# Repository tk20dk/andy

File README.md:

# andy
Audio interface for Krieger prototype board

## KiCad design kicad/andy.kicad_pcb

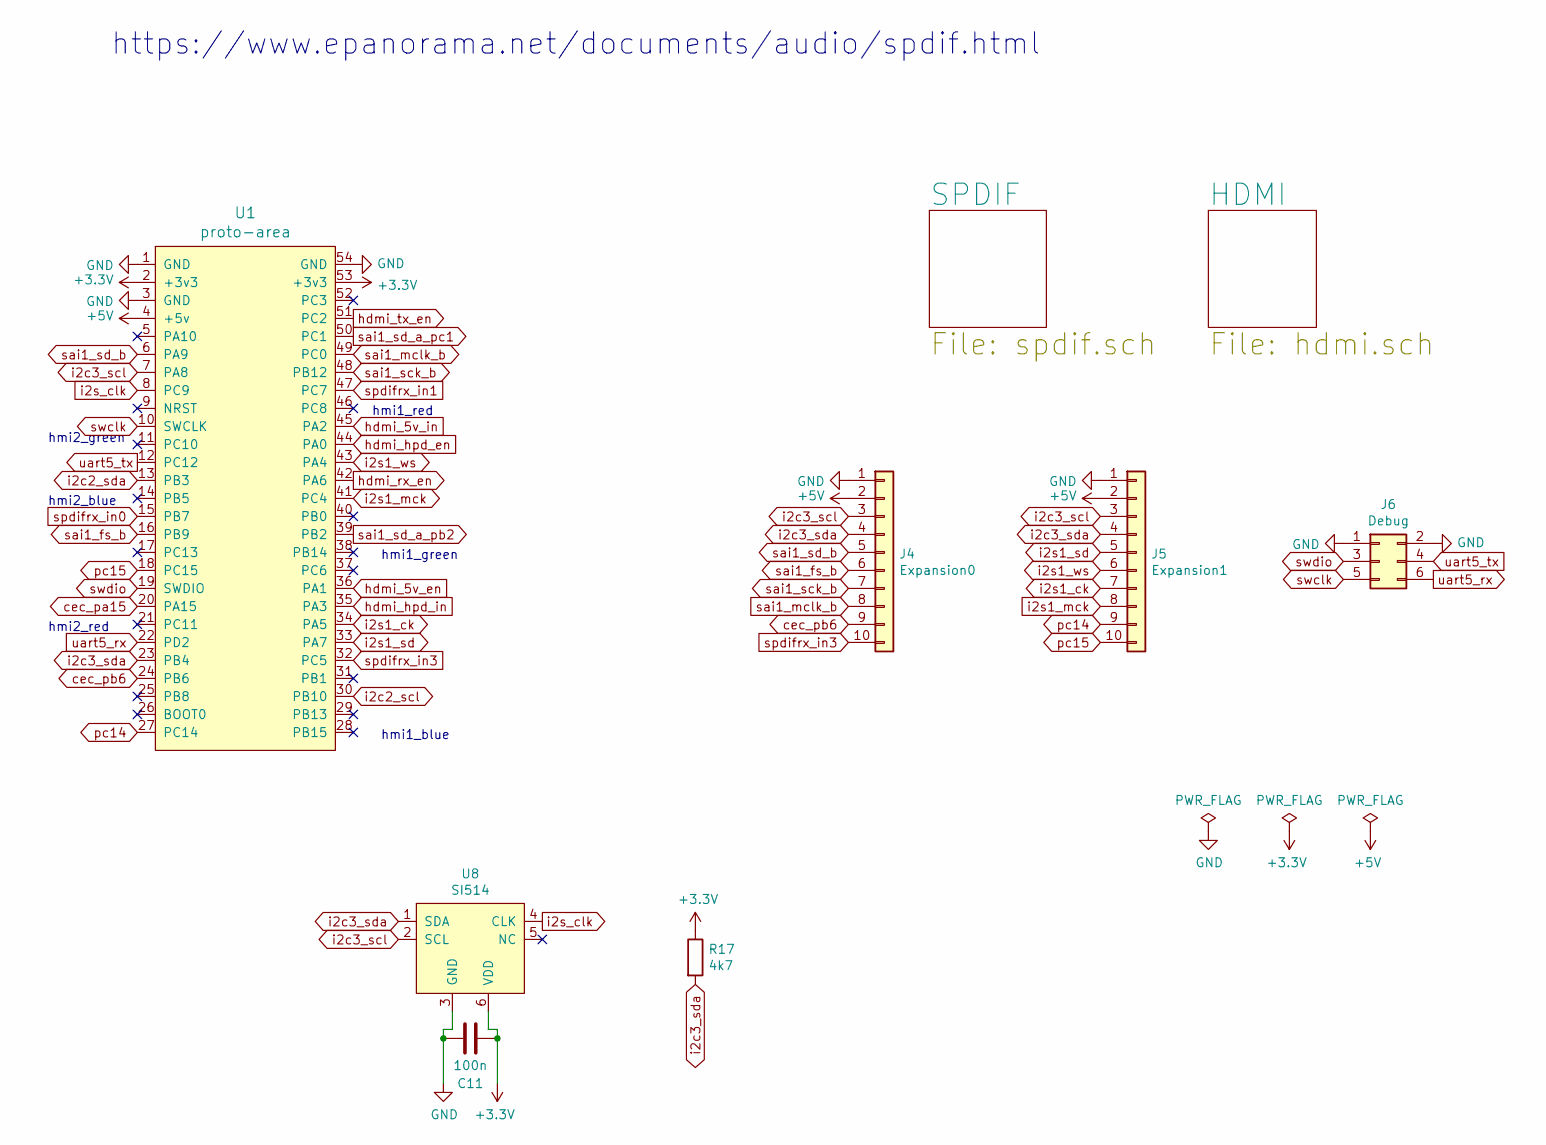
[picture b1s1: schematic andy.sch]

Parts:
C11: 100n; C_0603_1608Metric
J4: Expansion0; PinHeader_1x10_P2.54mm_Vertical
J5: Expansion1; PinHeader_1x10_P2.54mm_Vertical
J6: Debug; PinHeader_2x03_P2.54mm_Vertical
R17: 4k7; R_0603_1608Metric
U1: proto-area; proto-header
U8: SI514; Crystal_SMD_5032-6Pin_5.0x3.2mm

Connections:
+3V3: C11.2, R17.1, U1.2 (+3v3), U1.53 (+3v3), U8.6 (VDD); also elsewhere on the board
+5V: J4.2, J5.2, U1.4 (+5v); also elsewhere on the board
GND: C11.1, J4.1, J5.1, J6.1, J6.2, U1.1 (GND), U1.3 (GND), U1.54 (GND), U8.3 (GND); also elsewhere on the board
cec_pa15: U1.20 (PA15); also elsewhere on the board
cec_pb6: J4.9, U1.24 (PB6)
hdmi_5v_en: U1.36 (PA1); also elsewhere on the board
hdmi_5v_in: U1.45 (PA2); also elsewhere on the board
hdmi_hpd_en: U1.44 (PA0); also elsewhere on the board
hdmi_hpd_in: U1.35 (PA3); also elsewhere on the board
hdmi_rx_en: U1.42 (PA6); also elsewhere on the board
hdmi_tx_en: U1.51 (PC2); also elsewhere on the board
i2c2_scl: U1.30 (PB10); also elsewhere on the board
i2c2_sda: U1.13 (PB3); also elsewhere on the board
i2c3_scl: J4.3, J5.3, U1.7 (PA8), U8.2 (SCL)
i2c3_sda: J4.4, J5.4, R17.2, U1.23 (PB4), U8.1 (SDA)
i2s1_ck: J5.7, U1.34 (PA5)
i2s1_mck: J5.8, U1.41 (PC4)
i2s1_sd: J5.5, U1.33 (PA7)
i2s1_ws: J5.6, U1.43 (PA4)
i2s_clk: U1.8 (PC9), U8.4 (CLK)
pc14: J5.9, U1.27 (PC14)
pc15: J5.10, U1.18 (PC15)
sai1_fs_b: J4.6, U1.16 (PB9)
sai1_mclk_b: J4.8, U1.49 (PC0)
sai1_sck_b: J4.7, U1.48 (PB12)
sai1_sd_a_pb2: U1.39 (PB2); also elsewhere on the board
sai1_sd_a_pc1: U1.50 (PC1); also elsewhere on the board
sai1_sd_b: J4.5, U1.6 (PA9)
spdifrx_in0: U1.15 (PB7); also elsewhere on the board
spdifrx_in1: U1.47 (PC7); also elsewhere on the board
spdifrx_in3: J4.10, U1.32 (PC5)
swclk: J6.5, U1.10 (SWCLK)
swdio: J6.3, U1.19 (SWDIO)
uart5_rx: J6.6, U1.22 (PD2)
uart5_tx: J6.4, U1.12 (PC12)

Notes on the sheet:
https://www.epanorama.net/documents/audio/spdif.html
hmi2_green
hmi2_blue
hmi2_red
hmi1_blue
hmi1_green
hmi1_red

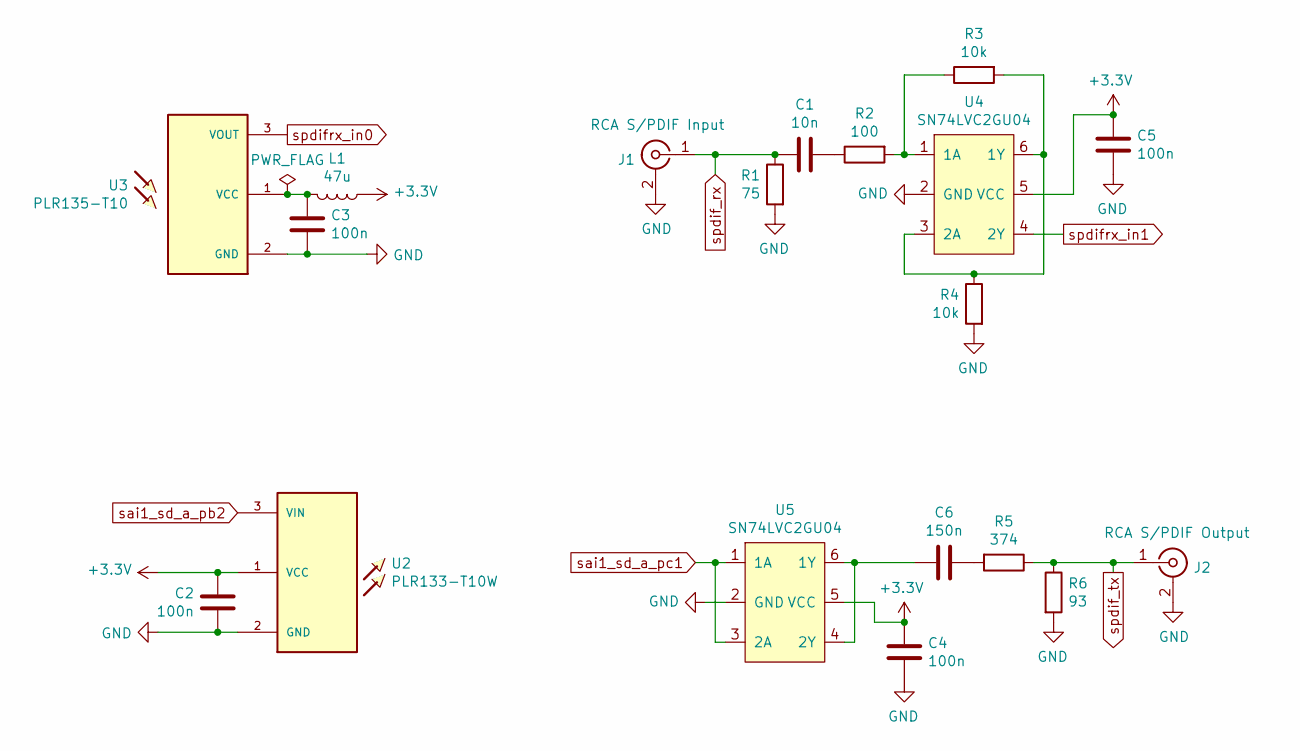
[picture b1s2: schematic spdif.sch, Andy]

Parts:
C1: 10n; C_0603_1608Metric
C2, C3, C4, C5: 100n; C_0603_1608Metric
C6: 150n; C_0603_1608Metric
J1: RCA S/PDIF Input; Audio-RCA
J2: RCA S/PDIF Output; Audio-RCA
L1: 47u; L_0805_2012Metric
R1: 75; R_0603_1608Metric
R2: 100; R_0603_1608Metric
R3, R4: 10k; R_0603_1608Metric
R5: 374; R_0603_1608Metric
R6: 93; R_0603_1608Metric
U2: PLR133-T10W; PLT133T10W
U3: PLR135-T10; PLR135T10
U4, U5: SN74LVC2GU04; SOT-23-6

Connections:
+3V3: C2.2, C4.2, C5.2, L1.2, U2.1 (VCC), U4.5 (VCC), U5.5 (VCC); also elsewhere on the board
GND: C2.1, C3.1, C4.1, C5.1, J1.2 (Ext), J2.2 (Ext), R1.2, R4.2, R6.2, U2.2 (GND), U3.2 (GND), U4.2 (GND), U5.2 (GND); also elsewhere on the board
unnamed: C1.2, R2.1
unnamed: C3.2, L1.1, U3.1 (VCC)
unnamed: C6.1, R5.2
unnamed: C6.2, U5.4 (2Y), U5.6 (1Y)
unnamed: R2.2, R3.1, U4.1 (1A)
unnamed: R3.2, R4.1, U4.3 (2A), U4.6 (1Y)
sai1_sd_a_pb2: U2.3 (VIN); also elsewhere on the board
sai1_sd_a_pc1: U5.1 (1A), U5.3 (2A); also elsewhere on the board
spdif_rx: C1.1, J1.1 (In), R1.1; also elsewhere on the board
spdif_tx: J2.1 (In), R5.1, R6.1; also elsewhere on the board
spdifrx_in0: U3.3 (VOUT); also elsewhere on the board
spdifrx_in1: U4.4 (2Y); also elsewhere on the board

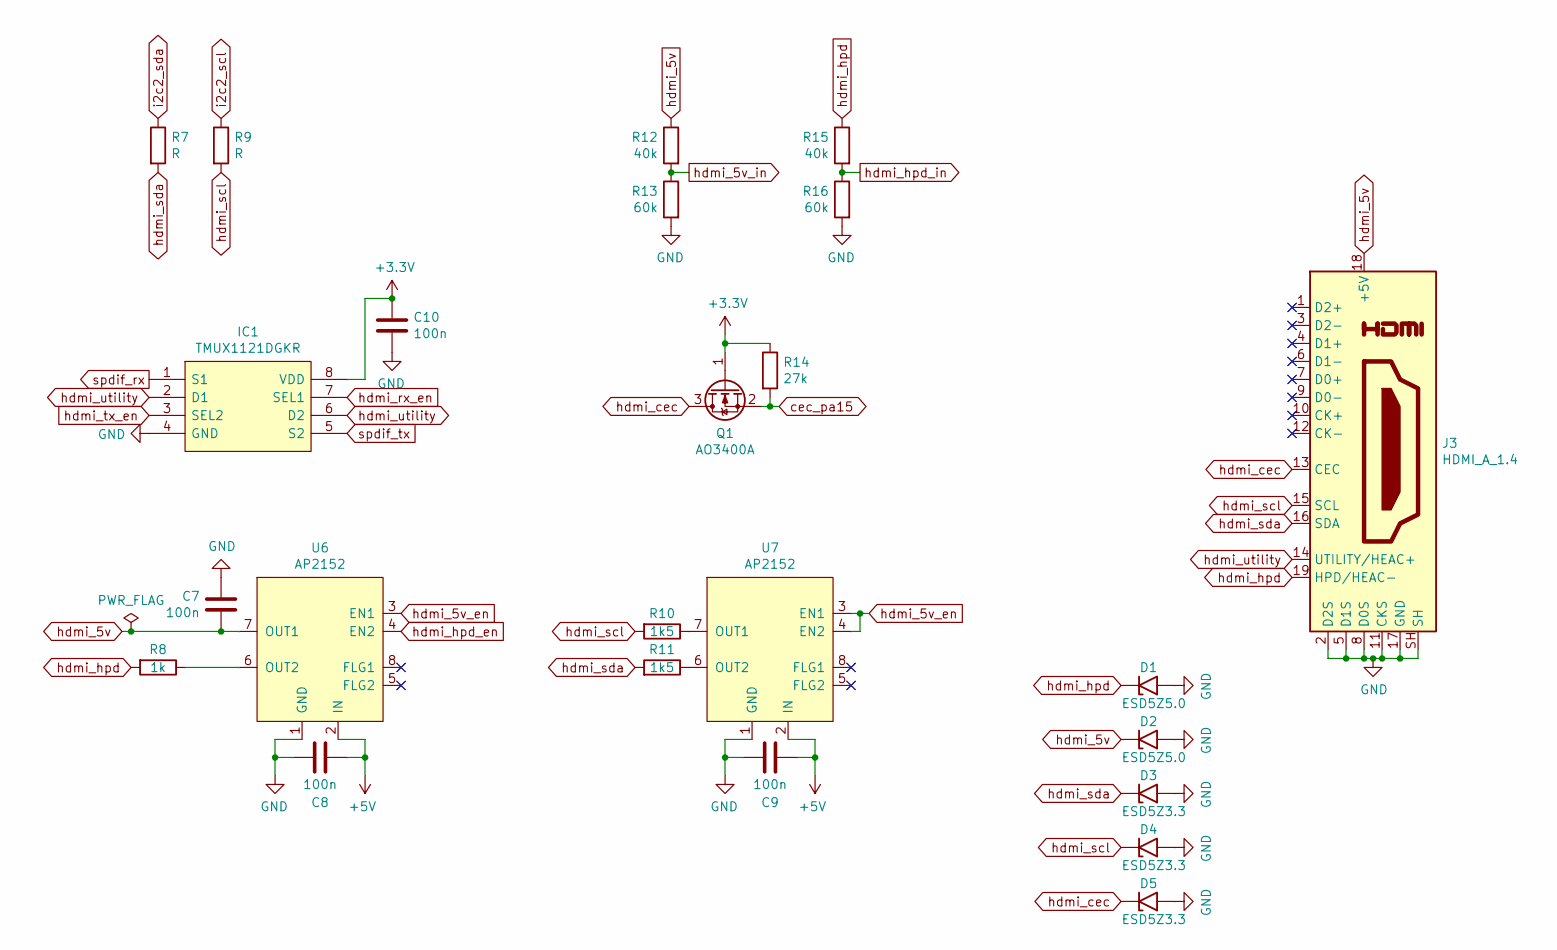
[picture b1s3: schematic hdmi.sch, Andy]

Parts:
C7, C8, C9, C10: 100n; C_0603_1608Metric
D1, D2: ESD5Z5.0; D_SOD-523
D3, D4, D5: ESD5Z3.3; D_SOD-523
IC1: TMUX1121DGKR; MSOP-8_3x3mm_P0.65mm
J3: HDMI_A_1.4; HDMI_A_19P
Q1: AO3400A; SOT-23
R7, R9: R; R_0603_1608Metric
R8: 1k; R_0603_1608Metric
R10, R11: 1k5; R_0603_1608Metric
R12, R15: 40k; R_0603_1608Metric
R13, R16: 60k; R_0603_1608Metric
R14: 27k; R_0603_1608Metric
U6, U7: AP2152; MSOP-8_3x3mm_P0.65mm

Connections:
+3V3: C10.1, IC1.8 (VDD), Q1.1 (G), R14.1; also elsewhere on the board
+5V: C8.2, C9.2, U6.2 (IN), U7.2 (IN); also elsewhere on the board
GND: C7.2, C8.1, C9.1, C10.2, D1.2 (A2), D2.2 (A2), D3.2 (A2), D4.2 (A2), D5.2 (A2), IC1.4 (GND), J3.2 (D2S), J3.5 (D1S), J3.8 (D0S), J3.11 (CKS), J3.17 (GND), J3.SH, R13.2, R16.2, U6.1 (GND), U7.1 (GND); also elsewhere on the board
unnamed: R8.1, U6.6 (OUT2)
unnamed: R10.1, U7.7 (OUT1)
unnamed: R11.1, U7.6 (OUT2)
cec_pa15: Q1.2 (S), R14.2; also elsewhere on the board
hdmi_5v: C7.1, D2.1 (A1), J3.18 (+5V), R12.1, U6.7 (OUT1)
hdmi_5v_en: U6.3 (EN1), U7.3 (EN1), U7.4 (EN2); also elsewhere on the board
hdmi_5v_in: R12.2, R13.1; also elsewhere on the board
hdmi_cec: D5.1 (A1), J3.13 (CEC), Q1.3 (D)
hdmi_hpd: D1.1 (A1), J3.19 (HPD/HEAC-), R8.2, R15.1
hdmi_hpd_en: U6.4 (EN2); also elsewhere on the board
hdmi_hpd_in: R15.2, R16.1; also elsewhere on the board
hdmi_rx_en: IC1.7 (SEL1); also elsewhere on the board
hdmi_scl: D4.1 (A1), J3.15 (SCL), R9.2, R10.2
hdmi_sda: D3.1 (A1), J3.16 (SDA), R7.2, R11.2
hdmi_tx_en: IC1.3 (SEL2); also elsewhere on the board
hdmi_utility: IC1.2 (D1), IC1.6 (D2), J3.14 (UTILITY/HEAC+)
i2c2_scl: R9.1; also elsewhere on the board
i2c2_sda: R7.1; also elsewhere on the board
spdif_rx: IC1.1 (S1); also elsewhere on the board
spdif_tx: IC1.5 (S2); also elsewhere on the board

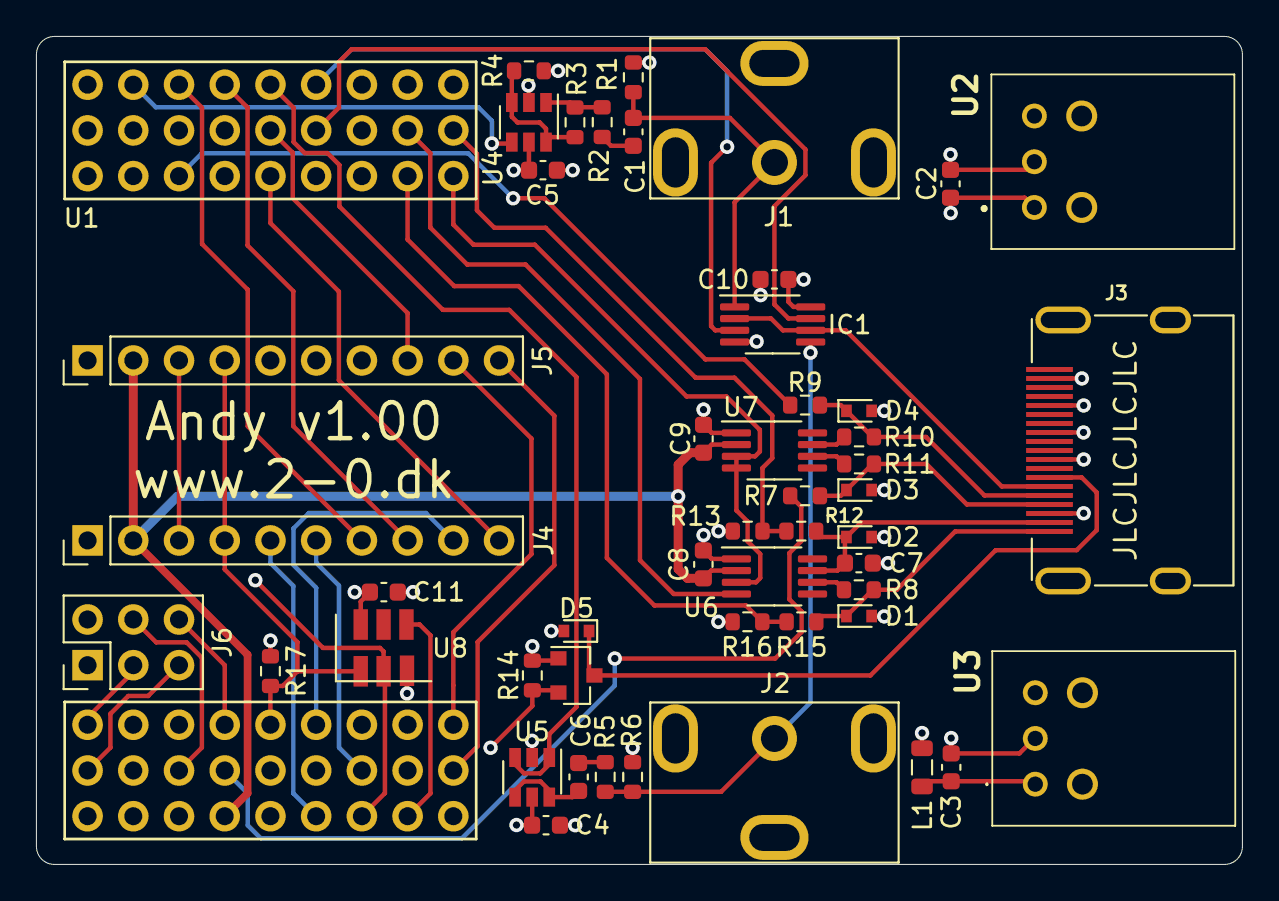
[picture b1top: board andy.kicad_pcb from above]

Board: 4 copper layers, 67.0 x 46.0 mm, 50 parts (0 on the bottom side), 52 nets.

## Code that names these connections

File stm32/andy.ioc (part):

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Mcu.Name=STM32F446R(C-E)Tx
Mcu.Package=LQFP64
Mcu.UserName=STM32F446RETx
PA0-WKUP.GPIOParameters=GPIO_Label
PA0-WKUP.GPIO_Label=HDMI_HPD_EN
PA0-WKUP.Signal=GPIO_Output
PA1.GPIOParameters=GPIO_Label
PA1.GPIO_Label=HDMI_5V_EN
PA1.Signal=GPIO_Output
PA11.Mode=Device_Only
PA11.Signal=USB_OTG_FS_DM
PA12.Mode=Device_Only
PA12.Signal=USB_OTG_FS_DP
PA13.Mode=Serial_Wire
PA13.Signal=SYS_JTMS-SWDIO
PA14.Mode=Serial_Wire
PA14.Signal=SYS_JTCK-SWCLK
PA15.GPIOParameters=GPIO_Label
PA15.GPIO_Label=CEC_PA15
PA15.Mode=CEC_Activate
PA15.Signal=CEC
PA2.GPIOParameters=GPIO_Label
PA2.GPIO_Label=HDMI_5V_IN
PA2.Signal=ADCx_IN2
PA3.GPIOParameters=GPIO_Label
PA3.GPIO_Label=HDMI_HPD_IN
PA3.Signal=ADCx_IN3
PA4.Mode=Half_Duplex_Master
PA4.Signal=I2S1_WS
PA5.Mode=Half_Duplex_Master
PA5.Signal=I2S1_CK
PA6.GPIOParameters=GPIO_Label
PA6.GPIO_Label=HDMI_RX_RN
PA6.Signal=GPIO_Output
PA7.Mode=Half_Duplex_Master
PA7.Signal=I2S1_SD
PA8.Mode=I2C
PA8.Signal=I2C3_SCL
PA9.Mode=SAI_B_MasterWithClock
PA9.Signal=SAI1_SD_B
PB10.Mode=I2C
PB10.Signal=I2C2_SCL
PB12.Mode=SAI_B_MasterWithClock
PB12.Signal=SAI1_SCK_B
PB14.GPIOParameters=GPIO_Label
PB14.GPIO_Label=HMI1_GREEN
PB14.Signal=GPIO_Output
PB15.GPIOParameters=GPIO_Label
PB15.GPIO_Label=HMI1_BLUE
PB15.Signal=GPIO_Output
PB2.GPIOParameters=GPIO_Label
PB2.GPIO_Label=SAI1_SD_A_PB2
PB2.Signal=GPIO_Output
PB3.Mode=I2C
PB3.Signal=I2C2_SDA
PB4.Mode=I2C
PB4.Signal=I2C3_SDA
PB6.GPIOParameters=GPIO_Label
PB6.GPIO_Label=CEC_PB6
PB6.Signal=GPIO_Output
PB7.Mode=IN0
PB7.Signal=SPDIFRX_IN0
PB9.Mode=SAI_B_MasterWithClock
PB9.Signal=SAI1_FS_B
PC0.Mode=SAI_B_MasterWithClock
PC0.Signal=SAI1_MCLK_B
PC1.GPIOParameters=GPIO_Label
PC1.GPIO_Label=SAI1_SD_A_PC1
PC1.Mode=SAI_A_SPDIF
PC1.Signal=SAI1_SD_A
PC10.GPIOParameters=GPIO_Label
PC10.GPIO_Label=HMI2_GREEN
PC10.Signal=GPIO_Output
PC11.GPIOParameters=GPIO_Label
PC11.GPIO_Label=HMI2_RED
PC11.Signal=GPIO_Output
PC12.Mode=Asynchronous
PC12.Signal=UART5_TX
PC14-OSC32_IN.GPIOParameters=GPIO_Label
PC14-OSC32_IN.GPIO_Label=PC14
PC14-OSC32_IN.Signal=GPIO_Output
PC15-OSC32_OUT.GPIOParameters=GPIO_Label
PC15-OSC32_OUT.GPIO_Label=PC15
PC15-OSC32_OUT.Signal=GPIO_Output
PC2.GPIOParameters=GPIO_Label
PC2.GPIO_Label=HDMI_TX_EN
PC2.Signal=GPIO_Output
PC4.Mode=Master_Clock_Activated
PC4.Signal=I2S1_MCK
PC5.Mode=IN3
PC5.Signal=SPDIFRX_IN3
PC7.Mode=IN1
PC7.Signal=SPDIFRX_IN1
PC8.GPIOParameters=GPIO_Label
PC8.GPIO_Label=HMI1_RED
PC8.Signal=GPIO_Output
PC9.Mode=Audio_ClockIn
PC9.Signal=I2S_CKIN
PD2.Mode=Asynchronous
PD2.Signal=UART5_RX
PH0-OSC_IN.Mode=HSE-External-Oscillator
PH0-OSC_IN.Signal=RCC_OSC_IN
PH1-OSC_OUT.Mode=HSE-External-Oscillator
PH1-OSC_OUT.Signal=RCC_OSC_OUT
board=custom

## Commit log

2021-06-05 Andy v1.00
